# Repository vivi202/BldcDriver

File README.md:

# BldcDriver
A simple bldc driver using drv8313.
## Features 
- capable of driving 2 bldc motors using 3xPWM 
- peak current of 2.5A
- Operating Supply Voltage Range 8V to 48V 
## Interactive bom
Click [here](https://htmlpreview.github.io/?https://github.com/vivi202/BldcDriver/blob/main/bom/ibom.html) to view interactive bom.

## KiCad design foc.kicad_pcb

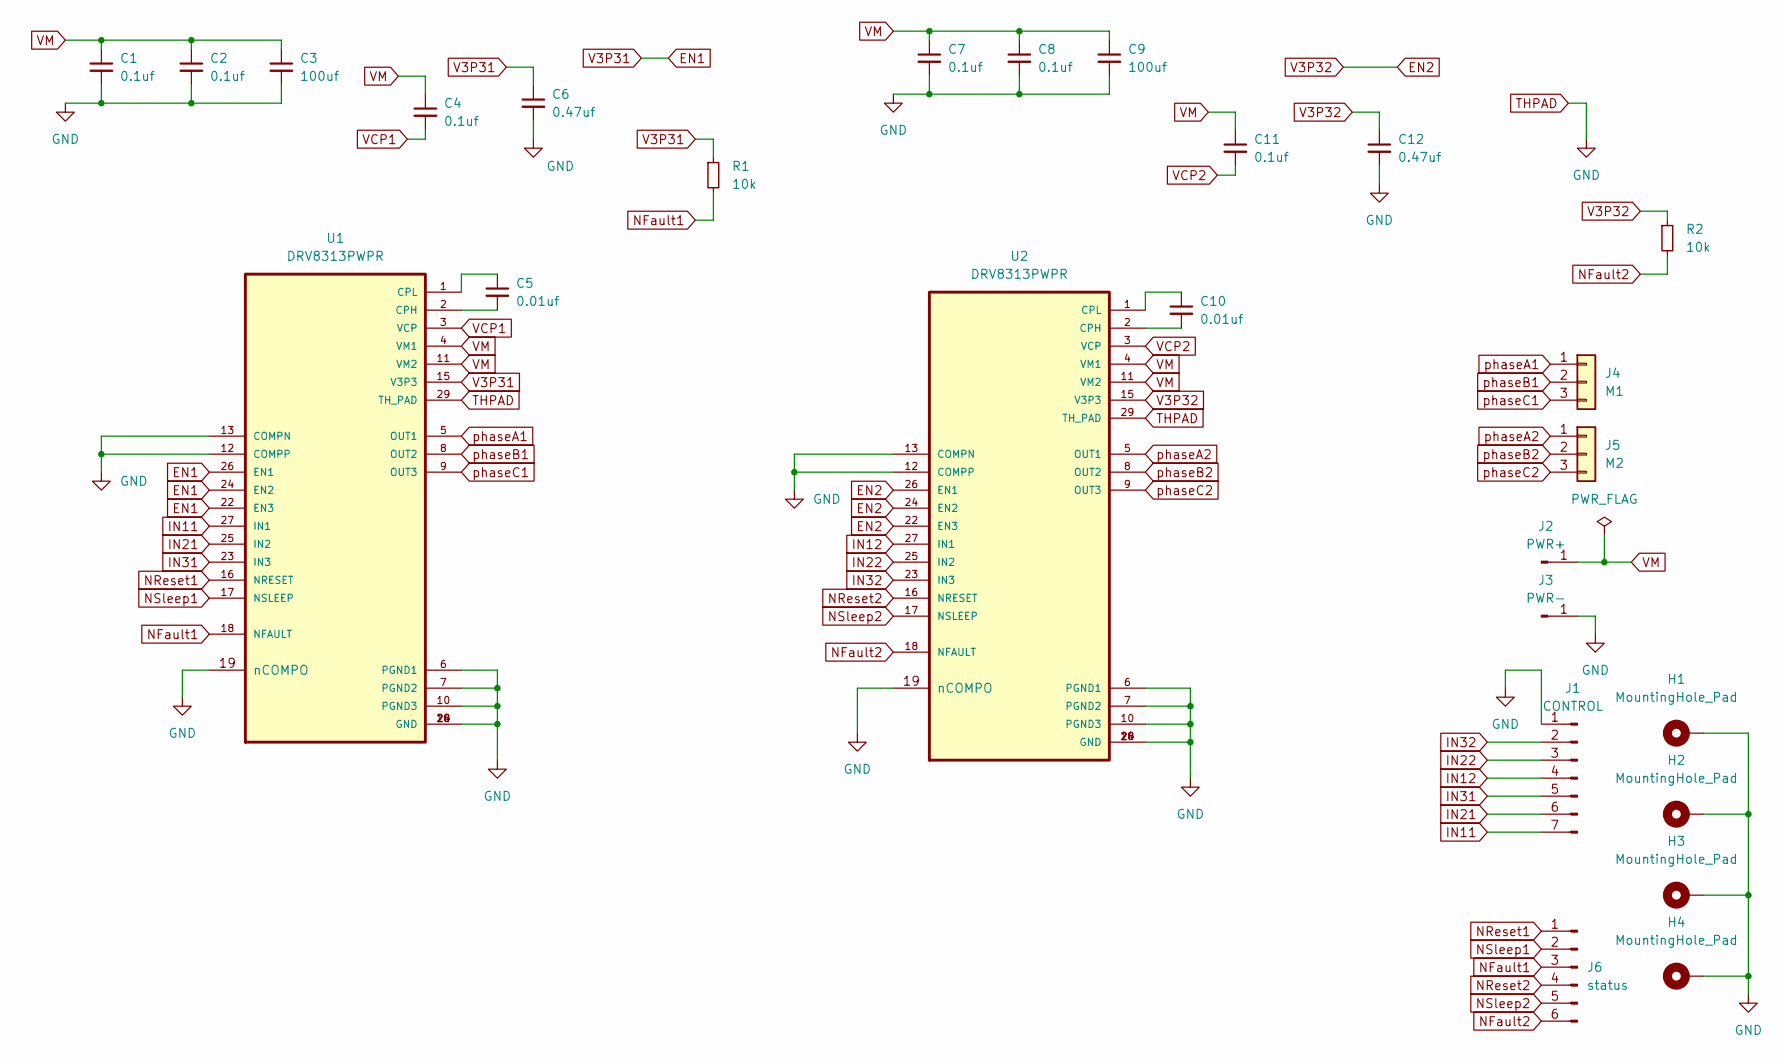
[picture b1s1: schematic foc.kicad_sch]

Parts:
C1, C2, C4, C7, C8, C11: 0.1uf; C_0603_1608Metric; LCSC C14663
C3, C9: 100uf; CP_Elec_8x10; LCSC C445063
C5, C10: 0.01uf; C_0603_1608Metric; LCSC C57112
C6, C12: 0.47uf; C_0603_1608Metric; LCSC C1623
H1, H2, H3, H4: MountingHole_Pad; MountingHole_2.5mm_Pad_Via
J1: CONTROL; PinHeader_1x07_P2.54mm_Horizontal
J2: PWR+; SolderWirePad_1x01_SMD_5x10mm
J3: PWR-; SolderWirePad_1x01_SMD_5x10mm
J4: M1; PinHeader_1x03_P2.54mm_Vertical
J5: M2; PinHeader_1x03_P2.54mm_Vertical
J6: status; PinHeader_1x06_P2.54mm_Horizontal
R1: 10k; R_0805_2012Metric; LCSC C25804
R2: 10k; R_0603_1608Metric; LCSC C25804
U1, U2: DRV8313PWPR; IC_TPS61196PWPRQ1; LCSC C92482

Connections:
EN1: C6.1, R1.1, U1.15 (V3P3), U1.22 (EN3), U1.24 (EN2), U1.26 (EN1)
EN2: C12.1, R2.1, U2.15 (V3P3), U2.22 (EN3), U2.24 (EN2), U2.26 (EN1)
IN11: J1.7, U1.27 (IN1)
IN12: J1.4, U2.27 (IN1)
IN21: J1.6, U1.25 (IN2)
IN22: J1.3, U2.25 (IN2)
IN31: J1.5, U1.23 (IN3)
IN32: J1.2, U2.23 (IN3)
NFault1: J6.3, R1.2, U1.18 (NFAULT)
NFault2: J6.6, R2.2, U2.18 (NFAULT)
NReset1: J6.1, U1.16 (NRESET)
NReset2: J6.4, U2.16 (NRESET)
NSleep1: J6.2, U1.17 (NSLEEP)
NSleep2: J6.5, U2.17 (NSLEEP)
unnamed: C5.1, U1.1 (CPL)
unnamed: C5.2, U1.2 (CPH)
unnamed: C10.1, U2.1 (CPL)
unnamed: C10.2, U2.2 (CPH)
THPAD: C1.2, C2.2, C3.2, C6.2, C7.2, C8.2, C9.2, C12.2, H1.1, H2.1, H3.1, H4.1, J1.1, J3.1, U1.6 (PGND1), U1.7 (PGND2), U1.10 (PGND3), U1.12 (COMPP), U1.13 (COMPN), U1.14 (GND), U1.19 (nCOMPO), U1.20 (GND), U1.28 (GND), U1.29 (TH_PAD), U2.6 (PGND1), U2.7 (PGND2), U2.10 (PGND3), U2.12 (COMPP), U2.13 (COMPN), U2.14 (GND), U2.19 (nCOMPO), U2.20 (GND), U2.28 (GND), U2.29 (TH_PAD)
VCP1: C4.2, U1.3 (VCP)
VCP2: C11.2, U2.3 (VCP)
VM: C1.1, C2.1, C3.1, C4.1, C7.1, C8.1, C9.1, C11.1, J2.1, U1.4 (VM1), U1.11 (VM2), U2.4 (VM1), U2.11 (VM2)
phaseA1: J4.1, U1.5 (OUT1)
phaseA2: J5.1, U2.5 (OUT1)
phaseB1: J4.2, U1.8 (OUT2)
phaseB2: J5.2, U2.8 (OUT2)
phaseC1: J4.3, U1.9 (OUT3)
phaseC2: J5.3, U2.9 (OUT3)

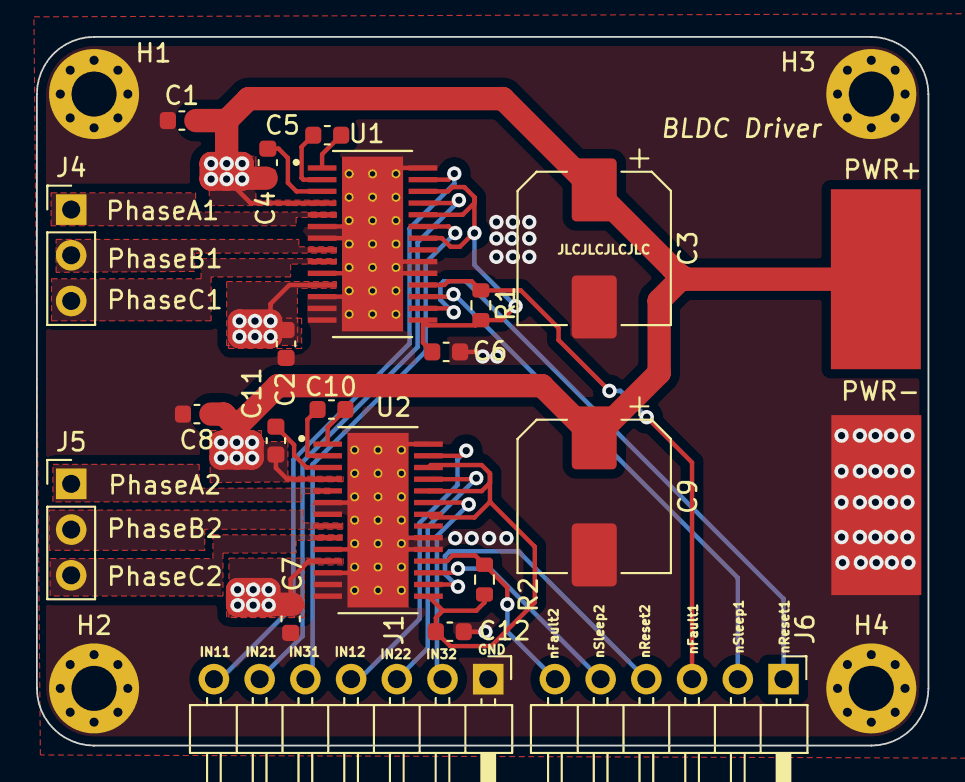
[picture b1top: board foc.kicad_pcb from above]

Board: 2 copper layers, 49.5 x 39.4 mm, 26 parts (0 on the bottom side), 28 nets.

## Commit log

2022-04-26 added picture of BldcDriver
2022-04-26 fixed copper pours
2022-04-26 Added interactive bom
